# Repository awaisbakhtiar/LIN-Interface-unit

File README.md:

Developed a LIN Interface Unit for camper van applications to sniff and monitor parameters on the LIN-Bus network. Designed the system to comply with ISO 7637 automotive transient protection standards, incorporating analog and digital isolation, overvoltage and undervoltage protection, and transient suppression circuitry for reliable operation in automotive environments. Integrated an ESP32 for wireless communication with a mobile application over Wi-Fi.

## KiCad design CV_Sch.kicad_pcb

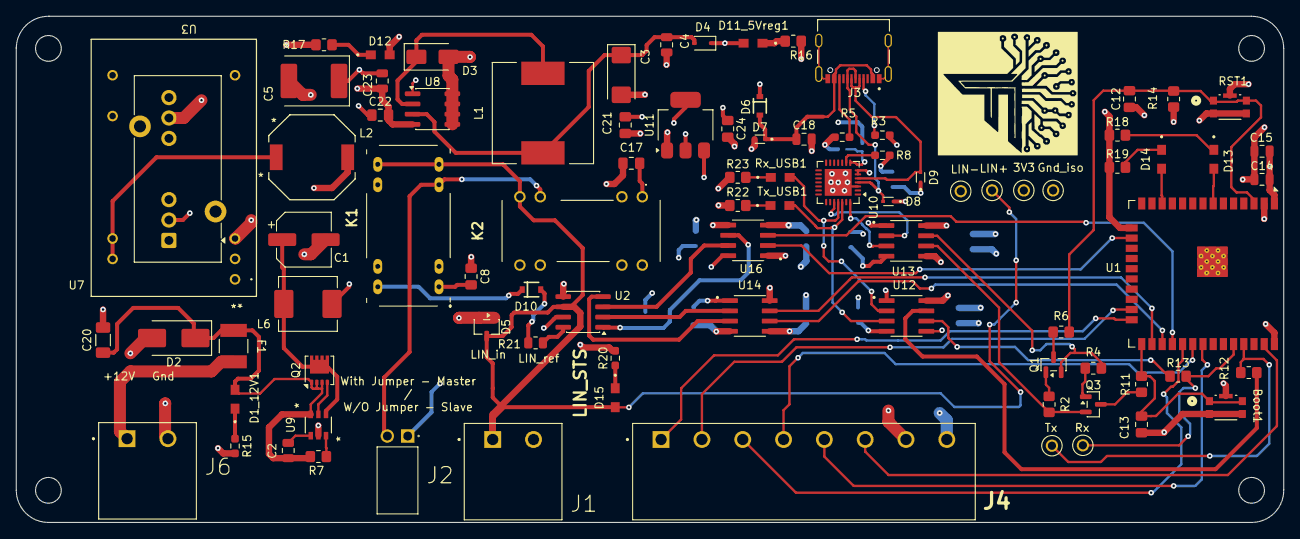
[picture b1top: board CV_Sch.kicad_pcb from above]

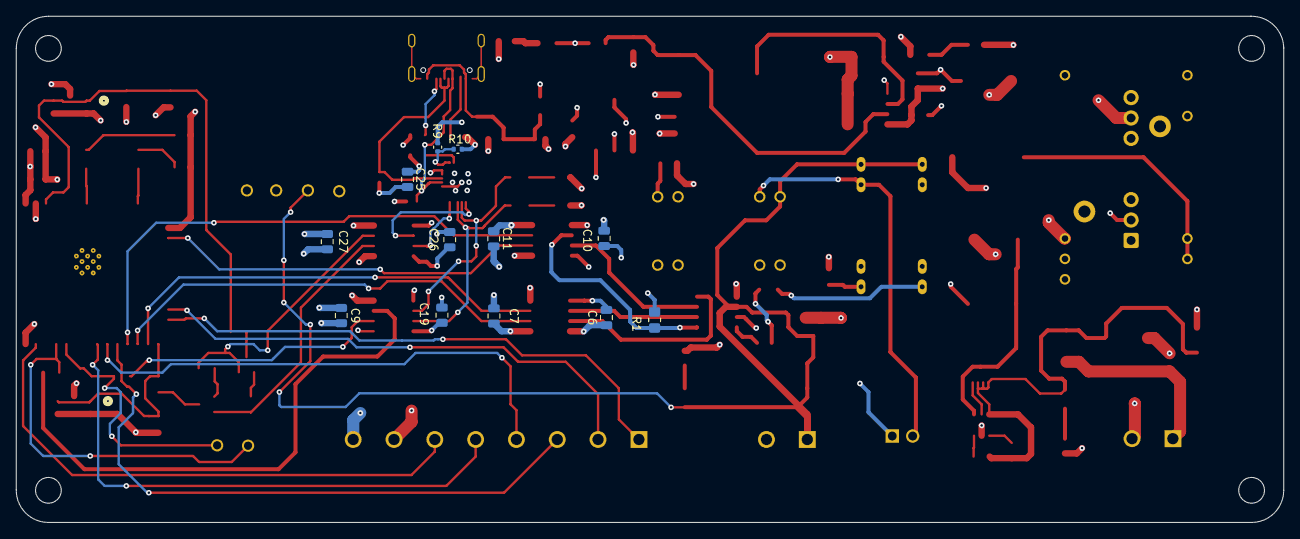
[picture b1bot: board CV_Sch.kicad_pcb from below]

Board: 4 copper layers, 157.8 x 63.0 mm, 104 parts (12 on the bottom side), 69 nets.

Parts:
Boot1: KMR223G LFG; KMR2_G_CNK_Y78B22310FP
C1: 220uF/25V; CP_Elec_6.3x7.7
C2, C4, C6, C7, C9, C10, C11, C14, C18, C19, C23, C26, C27: 100nF/50V; C_0805_2012Metric
C3: 100uF/10V; CP_EIA-6032-28_Kemet-C
C5: 100uF/25V; CP_EIA-7360-38_Kemet-E
C8: 1nF/50V; C_0805_2012Metric_Pad1.18x1.45mm_HandSolder
C12, C13, C21, C22, C24: 10uF/35V; C_0805_2012Metric_Pad1.18x1.45mm_HandSolder
C15: 22uF/16V; C_0805_2012Metric
C17: 220pF/100V; C_0805_2012Metric_Pad1.18x1.45mm_HandSolder
C20: 22nF/200V; C_1206_3216Metric_Pad1.33x1.80mm_HandSolder
C25: 4.7uF/16V; C_0805_2012Metric
D1_12V1, D11_5Vreg1, D12: APT2012SURCK; LED_APT2012SURCK
D2: TVS_58V; D_SMB_Handsoldering
D3: SS34; D_SMA
D4: BAT60A; D_SOD-323
D5: MMBZ27VCLT1G; SOT-23-3
D6: BAT20JFILM; SOD-323
D7, D8, D9: LESD5D5.0CT1G; TVS_LESD5D5.0CT1G
D10: MBR0520LT1G; SOD-323
D13, D14, D15: APT2012ZGC; LED_APT2012SURCK
F1: 1812L150/24MR; FUSE_1812L150&slash_24_LTF
H1, H2, H3, H4: MountingHole; MountingHole_3.2mm_M3
J1, J6: 1757242; PHOENIX_1757242
J2: M20-9750242; M20-97502XX
J3: TYPE-C-31-M-12; HRO_TYPE-C-31-M-12
J4: 1757307; PHOENIX_1757307
K1: HE722A1210
K2: 8L41-12-001
L1: 68uH; L_12x12mm_H6mm
L2: 12uH; IND_CDRH104_SUM
L6: 10uH/3A; L_TechFuse_SL0624
Q1, Q3: SS8050; SOT-23
Q2: DMT6008LFG; Diodes_PowerDI3333-8
R1, R2, R4, R14: 10k; R_0805_2012Metric_Pad1.20x1.40mm_HandSolder
R3, R5: 5.1k; R_0603_1608Metric_Pad0.98x0.95mm_HandSolder
R6, R11, R12, R13: 22R; R_0805_2012Metric_Pad1.20x1.40mm_HandSolder
R7: 100k; R_0805_2012Metric_Pad1.20x1.40mm_HandSolder
R8, R15, R20: 1k; R_0603_1608Metric_Pad0.98x0.95mm_HandSolder
R9: 22.1k; R_0402_1005Metric
R10: 47.5k; R_0402_1005Metric
R16: 330R; R_0805_2012Metric_Pad1.20x1.40mm_HandSolder
R17, R18, R19, R22, R23: 120R; R_0805_2012Metric_Pad1.20x1.40mm_HandSolder
R21: 1k; R_0805_2012Metric
RST1: KMR223G LFG; KMR2_G_CNK_Y78B22310FP
Rx_USB1: APT2012SURCK; LED_APT2012SURCK
TP1: RH-5000; TestPoint_RH-5001(black)
TP2, TP4: RH-5001; TestPoint_RH-5001(black)
TP3: RH-5004; TestPoint_RH-5001(black)
TP5: RH-5117; TestPoint_RH-5001(black)
TP6: RH-5116; TestPoint_RH-5001(black)
Tx_USB1: APT2012SURCK; LED_APT2012SURCK
U1: ESP32-WROOM-32E; ESP32-WROOM-32D
U2: TJA1021T/20/C,118; SOIC-8_3.9x4.9mm_P1.27mm
U3: JCG1212S3V3; RLA_JCG12_JCG15_SINGLE_XPR
U7: TMR 12-1210WI; Converter_DCDC_TRACO_TMR10-24xxWIR_48xxWIR_72xxWIR_THT
U8: XL1509-5.0; SOIC-8_3.9x4.9mm_P1.27mm
U9: AP74700QW6-7; SOT26_DIO
U10: CP2102N-A02-GQFN28R; QFN-28-1EP_5x5mm_P0.5mm_EP3.35x3.35mm
U11: AMS1117-3.3; SOT-223-3_TabPin2
U12: ISO7421DR; SOIC127P599X175-8N
U13, U14, U16: ISO7420FED; SOIC127P599X175-8N

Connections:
3.3V_iso: C7.2, C9.2, C11.2, C14.1, C15.2, C27.2, D12.2, J4.07, R14.1, TP1.TP, U1.2 (VDD), U3.14 (+VOUT), U7.6 (+Vout), U12.8 (VCC2), U13.8 (VCC2), U14.8 (VCC2), U16.1 (VCC1)
5V_Ext: C6.1, C10.1, C21.1, D4.1 (K), D6.C, D11_5Vreg1.2, R1.2, R9.2, U11.3 (VI), U14.1 (VCC1), U16.8 (VCC2)
+3.3V_EXT: C19.2, C24.1, C25.1, C26.1, R8.2, U10.6 (VDD), U10.7 (VREGIN), U11.2 (VO), U12.1 (VCC1), U13.1 (VCC1)
+5V_USB: C18.1, D6.A, D7.1, J3.A4_B9 (VBUS), J3.B4_A9 (VBUS)
+12V_Ext: C5.1, C22.1, C23.1, J2.1, L2.2, L6.2, U2.7 (VBAT), U7.2 (+Vin), U8.1 (VIN)
/ESP32_Interface/EN: C12.2, R6.2, R14.2, RST1.1, RST1.2, U1.3 (EN)
/ESP32_Interface/GPIO_1_Ext: J4.01, U1.24 (IO2)
/ESP32_Interface/GPIO_2_Ext: J4.02, U1.23 (IO15)
/ESP32_Interface/IO0: Boot1.1, Boot1.2, C13.2, R11.1, U1.25 (IO0)
/ESP32_Interface/MISO: J4.05, U1.31 (IO19)
/ESP32_Interface/MOSI: J4.06, U1.37 (IO23)
/ESP32_Interface/RXD0: R13.2, TP6.TP, U1.34 (RXD0/IO3)
/ESP32_Interface/SCLK: J4.04, U1.30 (IO18)
/ESP32_Interface/SPI_CS: J4.03, U1.29 (IO5)
/ESP32_Interface/TXD0: R12.2, TP5.TP, U1.35 (TXD0/IO1)
/LIN Interface/LIN_Input: D5.3 (A), D15.2, J1.01, K1.7 (COM_1), K1.8 (COM_2), K2.7 (COM_1), TP3.TP, U2.6 (LIN)
/Power and USB Interface (page 3)/RX_CP: Rx_USB1.2, U10.25 (RXD), U12.2 (OUTA)
/Power and USB Interface (page 3)/TX_CP: Tx_USB1.2, U10.26 (TXD), U12.3 (INB)
Gnd_Ext: C1.2, C3.2, C4.2, C5.2, C6.2, C8.2, C10.2, C17.2, C18.2, C19.1, C20.2, C21.2, C22.2, C23.2, C24.2, C25.2, C26.2, D2.2 (A2), D3.2 (A), D5.1 (K), D5.2 (K), D7.2, D8.1, D9.1, J1.02, J3.A1_B12 (GND), J3.B1_A12 (GND), J3.S1 (SHIELD), J3.S2 (SHIELD), J3.S3 (SHIELD), J3.S4 (SHIELD), J6.02, K1.2 (COIL+), K2.2 (COIL_1), R3.1, R5.1, R10.2, R15.1, R16.1, R20.1, R22.1, R23.1, TP4.TP, U2.5 (GND), U3.2 (-VIN), U3.3 (-VIN), U7.1 (-Vin), U8.4 (~EN), U8.5 (GND), U8.6 (GND), U8.7 (GND), U8.8 (GND), U9.2 (GND), U10.3 (GND), U10.29 (GND), U11.1 (GND), U12.4 (GND1), U13.4 (GND1), U14.4 (GND1), U16.5 (GND2)
Gnd_iso: Boot1.3, Boot1.4, Boot1.5, C7.1, C9.1, C11.1, C12.1, C13.1, C14.2, C15.1, C27.1, J4.08, R17.1, R18.1, R19.1, RST1.3, RST1.4, RST1.5, TP2.TP, U1.1 (GND), U1.15 (GND), U1.38 (GND), U1.39 (GND), U3.16 (-VOUT), U7.7 (-Vout), U12.5 (GND2), U13.5 (GND2), U14.5 (GND2), U16.4 (GND1)
unnamed: D1_12V1.1, R15.2
unnamed: C2.2, C20.1, D1_12V1.2, D2.1 (A1), F1.2, Q2.1 (S), Q2.2 (S), Q2.3 (S), R7.2, U9.6 (ANODE)
unnamed: D3.1 (K), L1.1, U8.2 (OUT)
unnamed: C3.1, C4.1, D4.2 (A), L1.2, U8.3 (FB)
unnamed: D10.A, R21.1
unnamed: D11_5Vreg1.1, R16.2
unnamed: D12.1, R17.2
unnamed: D13.1, R18.2
unnamed: D14.1, R19.2
unnamed: D15.1, R20.2
unnamed: F1.1, J6.01
unnamed: J3.A5 (CC1), R3.2
unnamed: J3.B5 (CC2), R5.2
unnamed: D9.2, J3.A7 (DN1), J3.B7 (DN2), U10.5 (D-)
unnamed: D8.2, J3.A6 (DP1), J3.B6 (DP2), U10.4 (D+)
unnamed: J2.2, K1.6 (COIL-), K2.6 (COIL_2)
unnamed: C8.1, K1.1 (NO_1)
unnamed: D10.C, K1.14 (NO_2)
unnamed: C17.1, K2.1 (NC)
unnamed: L2.1, U3.22 (+VIN), U3.23 (+VIN)
unnamed: Q1.1 (B), R2.1
unnamed: Q1.3 (C), R6.1
unnamed: C1.1, L6.1, Q2.5 (D), U9.4 (CATHODE)
unnamed: Q2.4 (G), U9.5 (GATE)
unnamed: Q3.1 (B), R4.1
unnamed: Q3.3 (C), R11.2
unnamed: R22.2, Tx_USB1.1
unnamed: R23.2, Rx_USB1.1
unnamed: D14.2, U1.12 (IO27)
unnamed: D13.2, U1.7 (IO35)
unnamed: R21.2, U2.8 (INH)
unnamed: R7.1, U9.3 (EN)
unnamed: C2.1, U9.1 (VCP)
unnamed: R9.1, R10.1, U10.8 (VBUS)
unnamed: U10.28 (~DTR), U13.3 (INB)
unnamed: R8.1, U10.9 (~RST)
unnamed: U10.24 (~RTS), U13.2 (INA)
unnamed: U2.2 (~SLP), U14.2 (INA)
unnamed: U2.4 (TXD), U14.3 (INB)
unnamed: U2.3 (~WAKE), U16.7 (OUTA)
unnamed: R1.1, U2.1 (RXD), U16.6 (OUTB)
RxD_ESP32: R13.1, U12.6 (OUTB)
RxLIN_ESP32: U1.27 (IO16), U14.6 (OUTB)
TxD_ESP32: R12.1, U12.7 (INA)
TxLIN_ESP32: U1.28 (IO17), U16.3 (INB)
nDTR_ESP32: Q3.2 (E), R2.2, U13.6 (OUTB)
nRTS_ESP32: Q1.2 (E), R4.2, U13.7 (OUTA)
nSLP_ESP32: U1.26 (IO4), U14.7 (OUTA)
nWAKE_ESP32: U1.16 (IO13), U16.2 (INA)
